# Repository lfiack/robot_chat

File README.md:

# robot_chat
My (as a prof) take at building a cat/mouse robot

## Make the project work
This project uses a submodule for the KiCAD library. To get it properly, use the `--recursive` option when cloning the repo :

```bash
git clone --recursive git@github.com:lfiack/robot_chat.git
```

If you forgot the `--recursive` option (as I do quite often), you can type the following command :

```bash
git submodule update --init --recursive
```

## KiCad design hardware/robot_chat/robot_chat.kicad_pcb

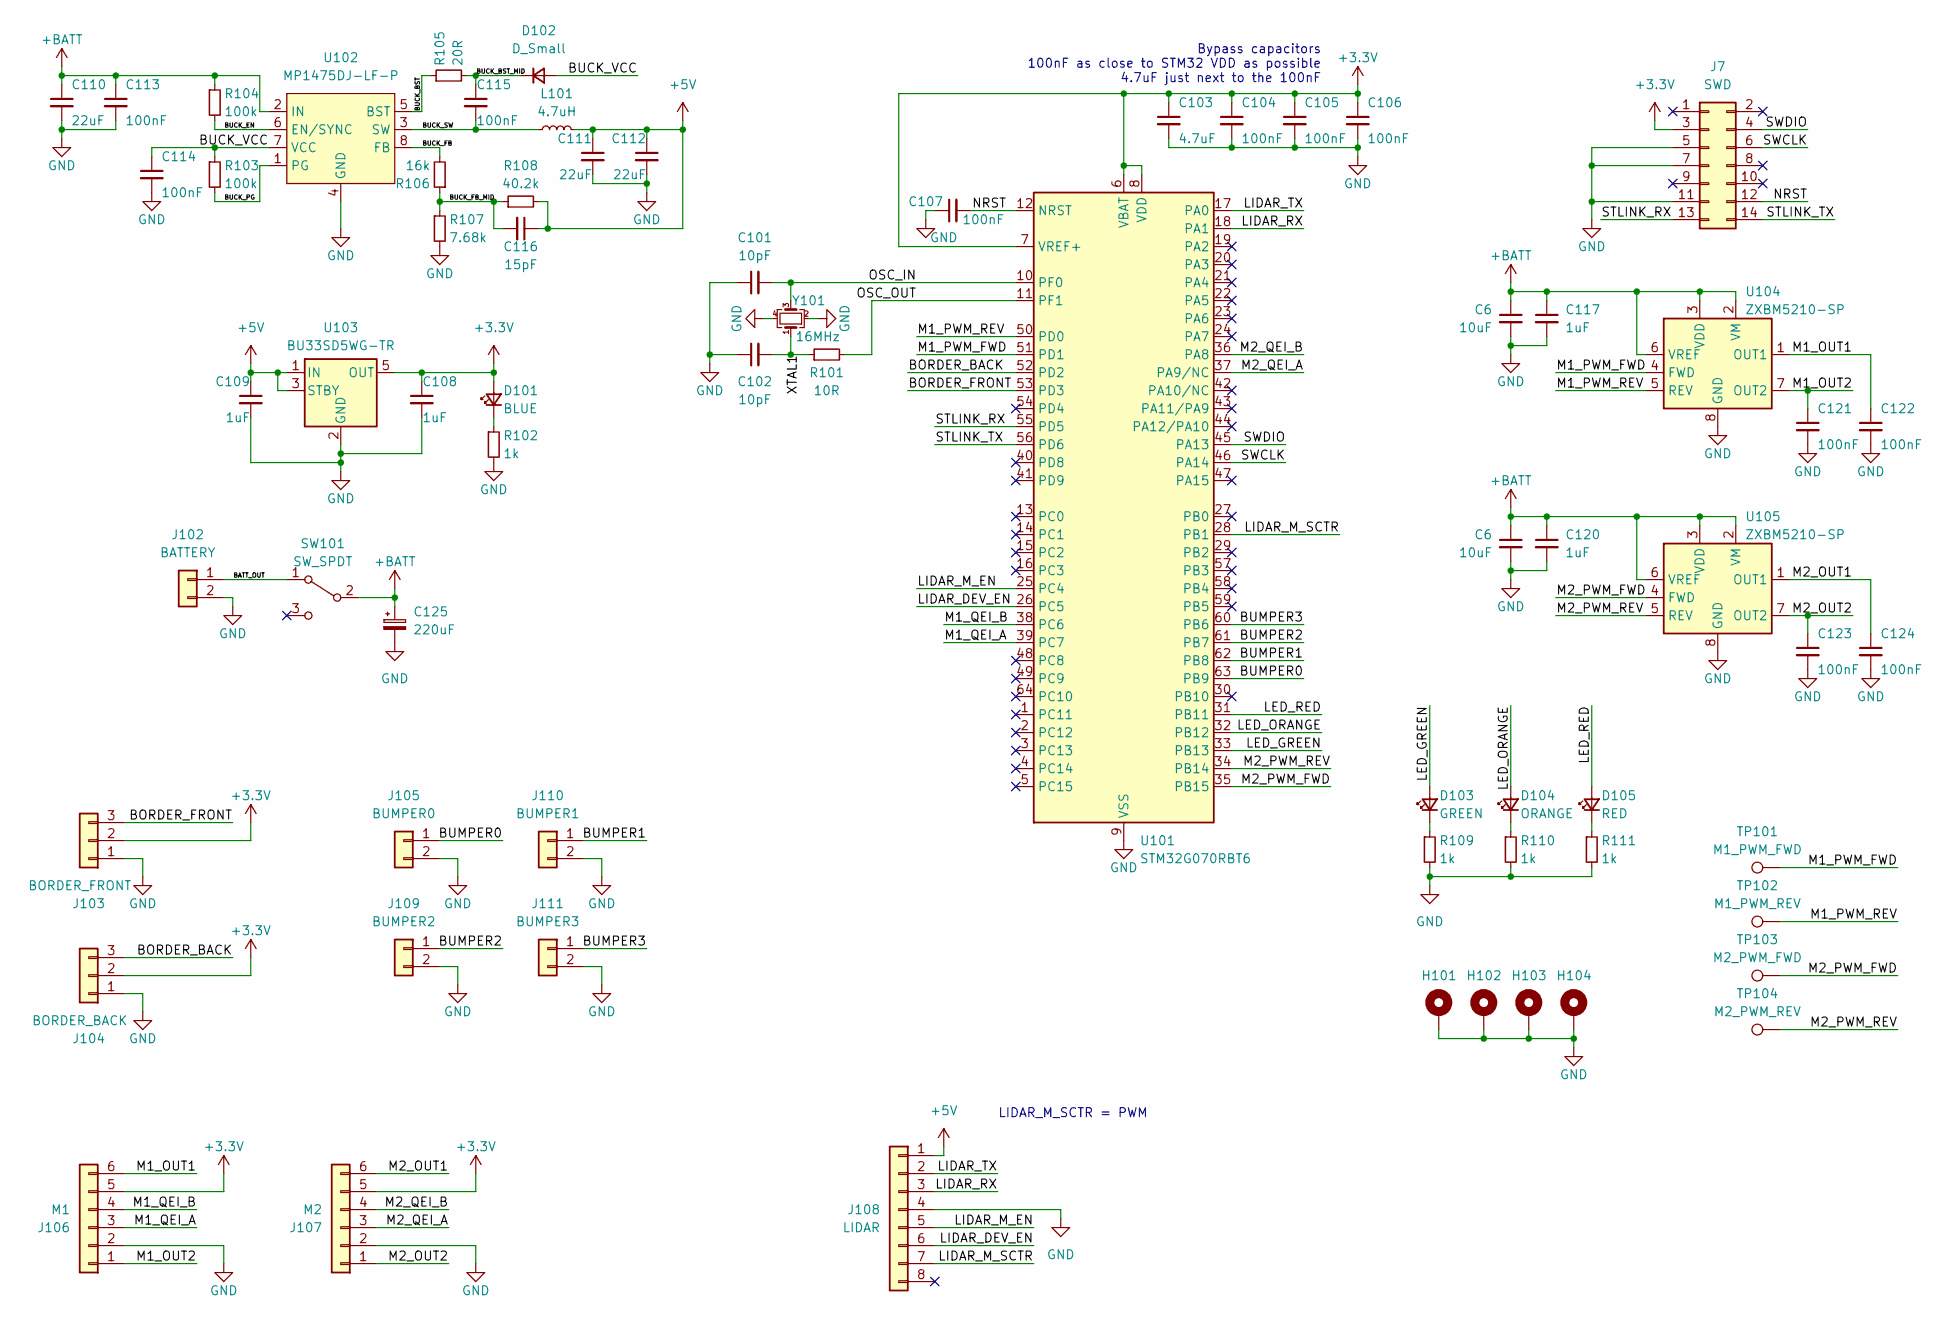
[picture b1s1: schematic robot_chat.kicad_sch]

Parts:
C6: 10uF; C_0603_1608Metric_Pad1.08x0.95mm_HandSolder; Farnell 2113070
C101, C102: 10pF; C_0603_1608Metric
C103: 4.7uF; C_0603_1608Metric
C104, C105, C106, C107, C113, C114, C115, C121, C122, C123, C124: 100nF; C_0603_1608Metric
C108, C109, C117, C120: 1uF; C_0603_1608Metric
C110, C111, C112: 22uF; C_0805_2012Metric
C116: 15pF; C_0603_1608Metric
C125: 220uF; CP_Elec_8x10.5
D101: BLUE; LED_0603_1608Metric
D102: D_Small; D_SOD-323
D103: GREEN; LED_0603_1608Metric
D104: ORANGE; LED_0603_1608Metric
D105: RED; LED_0603_1608Metric
H101, H102, H103, H104: MountingHole_Pad; MountingHole_3.2mm_M3_Pad_Via
J7: Conn_02x07_Odd_Even; PinHeader_2x07_P1.27mm_Vertical_SMD; Farnell 3226055
J102: BATTERY; JST_XH_S2B-XH-A_1x02_P2.50mm_Horizontal
J103: BORDER_FRONT; JST_XH_S3B-XH-A_1x03_P2.50mm_Horizontal
J104: BORDER_BACK; JST_XH_S3B-XH-A_1x03_P2.50mm_Horizontal
J105: BUMPER0; JST_XH_S2B-XH-A_1x02_P2.50mm_Horizontal
J106: M1; JST_XH_S6B-XH-A_1x06_P2.50mm_Horizontal
J107: M2; JST_XH_S6B-XH-A_1x06_P2.50mm_Horizontal
J108: LIDAR; JST_XH_S8B-XH-A_1x08_P2.50mm_Horizontal
J109: BUMPER2; JST_XH_S2B-XH-A_1x02_P2.50mm_Horizontal
J110: BUMPER1; JST_XH_S2B-XH-A_1x02_P2.50mm_Horizontal
J111: BUMPER3; JST_XH_S2B-XH-A_1x02_P2.50mm_Horizontal
L101: 4.7uH; L_1008_2520Metric; Farnell 2530076
R101: 10R; R_0603_1608Metric
R102, R109, R110, R111: 1k; R_0603_1608Metric
R103, R104: 100k; R_0603_1608Metric
R105: 20R; R_0603_1608Metric
R106: 16k; R_0603_1608Metric
R107: 7.68k; R_0603_1608Metric
R108: 40.2k; R_0603_1608Metric
SW101: SW_SPDT; Toggle_Switch
TP101: M1_PWM_FWD; TestPoint_Pad_D1.5mm
TP102: M1_PWM_REV; TestPoint_Pad_D1.5mm
TP103: M2_PWM_FWD; TestPoint_Pad_D1.5mm
TP104: M2_PWM_REV; TestPoint_Pad_D1.5mm
U101: STM32G070RBT6; LQFP-64_10x10mm_P0.5mm
U102: MP1475DJ-LF-P; TSOT-23-8
U103: BU33SD5WG-TR; SOT-23-5
U104, U105: ZXBM5210-SP; Diodes_SO-8EP
Y101: 16MHz; Crystal_SMD_EuroQuartz_MT-4Pin_3.2x2.5mm; Farnell 2853935

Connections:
+3.3V: C103.1, C104.1, C105.1, C106.1, C108.1, D101.2 (A), J7.3, J103.2, J104.2, J106.5, J107.5, U101.6 (VBAT), U101.7 (VREF+), U101.8 (VDD), U103.5 (OUT)
+5V: C109.1, C111.1, C112.1, C116.1, J108.1, L101.2, R108.2, U103.1 (IN), U103.3 (STBY)
+BATT: C6.1, C110.1, C113.1, C117.1, C120.1, C125.1, R104.1, SW101.2 (B), U102.2 (IN), U104.2 (VM), U104.3 (VDD), U104.6 (VREF), U105.2 (VM), U105.3 (VDD), U105.6 (VREF); also elsewhere on the board
/BATT_OUT: J102.1, SW101.1 (A)
/BORDER_BACK: J104.3, U101.52 (PD2)
/BORDER_FRONT: J103.3, U101.53 (PD3)
/BUCK_BST: R105.1, U102.5 (BST)
/BUCK_BST_MID: C115.1, D102.1 (K), R105.2
/BUCK_EN: R104.2, U102.6 (EN/SYNC)
/BUCK_FB: R106.2, U102.8 (FB)
/BUCK_FB_MID: C116.2, R106.1, R107.1, R108.1
/BUCK_PG: R103.2, U102.1 (PG)
/BUCK_SW: C115.2, L101.1, U102.3 (SW)
/BUCK_VCC: C114.1, D102.2 (A), R103.1, U102.7 (VCC)
/BUMPER0: J105.1, U101.63 (PB9)
/BUMPER1: J110.1, U101.62 (PB8)
/BUMPER2: J109.1, U101.61 (PB7)
/BUMPER3: J111.1, U101.60 (PB6)
/LED_GREEN: D103.2 (A), U101.33 (PB13)
/LED_ORANGE: D104.2 (A), U101.32 (PB12)
/LED_RED: D105.2 (A), U101.31 (PB11)
/LIDAR_DEV_EN: J108.6, U101.26 (PC5)
/LIDAR_M_EN: J108.5, U101.25 (PC4)
/LIDAR_M_SCTR: J108.7, U101.28 (PB1)
/LIDAR_RX: J108.3, U101.18 (PA1)
/LIDAR_TX: J108.2, U101.17 (PA0)
/M1_OUT1: C122.1, J106.6, U104.1 (OUT1)
/M1_OUT2: C121.1, J106.1, U104.7 (OUT2)
/M1_PWM_FWD: TP101.1, U101.51 (PD1), U104.4 (FWD)
/M1_PWM_REV: TP102.1, U101.50 (PD0), U104.5 (REV)
/M1_QEI_A: J106.3, U101.39 (PC7)
/M1_QEI_B: J106.4, U101.38 (PC6)
/M2_OUT1: C124.1, J107.6, U105.1 (OUT1)
/M2_OUT2: C123.1, J107.1, U105.7 (OUT2)
/M2_PWM_FWD: TP103.1, U101.35 (PB15), U105.4 (FWD)
/M2_PWM_REV: TP104.1, U101.34 (PB14), U105.5 (REV)
/M2_QEI_A: J107.3, U101.37 (PA9/NC)
/M2_QEI_B: J107.4, U101.36 (PA8)
/NRST: C107.2, J7.12, U101.12 (NRST)
/OSC_IN: C101.2, U101.10 (PF0), Y101.3
/OSC_OUT: R101.2, U101.11 (PF1)
/STLINK_RX: J7.13, U101.55 (PD5)
/STLINK_TX: J7.14, U101.56 (PD6)
/SWCLK: J7.6, U101.46 (PA14)
/SWDIO: J7.4, U101.45 (PA13)
/XTAL1: C102.2, R101.1, Y101.1
GND: C6.2, C101.1, C102.1, C103.2, C104.2, C105.2, C106.2, C107.1, C108.2, C109.2, C110.2, C111.2, C112.2, C113.2, C114.2, C117.2, C120.2, C121.2, C122.2, C123.2, C124.2, C125.2, H101.1, H102.1, H103.1, H104.1, J7.5, J7.7, J7.11, J102.2, J103.1, J104.1, J105.2, J106.2, J107.2, J108.4, J109.2, J110.2, J111.2, R102.2, R107.2, R109.2, R110.2, R111.2, U101.9 (VSS), U102.4 (GND), U103.2 (GND), U104.8 (GND), U104.9 (GND), U105.8 (GND), U105.9 (GND), Y101.2, Y101.4; also elsewhere on the board
unnamed: D101.1 (K), R102.1
unnamed: D103.1 (K), R109.1
unnamed: D104.1 (K), R110.1
unnamed: D105.1 (K), R111.1

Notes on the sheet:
Bypass capacitors 100nF as close to STM32 VDD as possible 4.7uF just next to the 100nF
LIDAR_M_SCTR = PWM

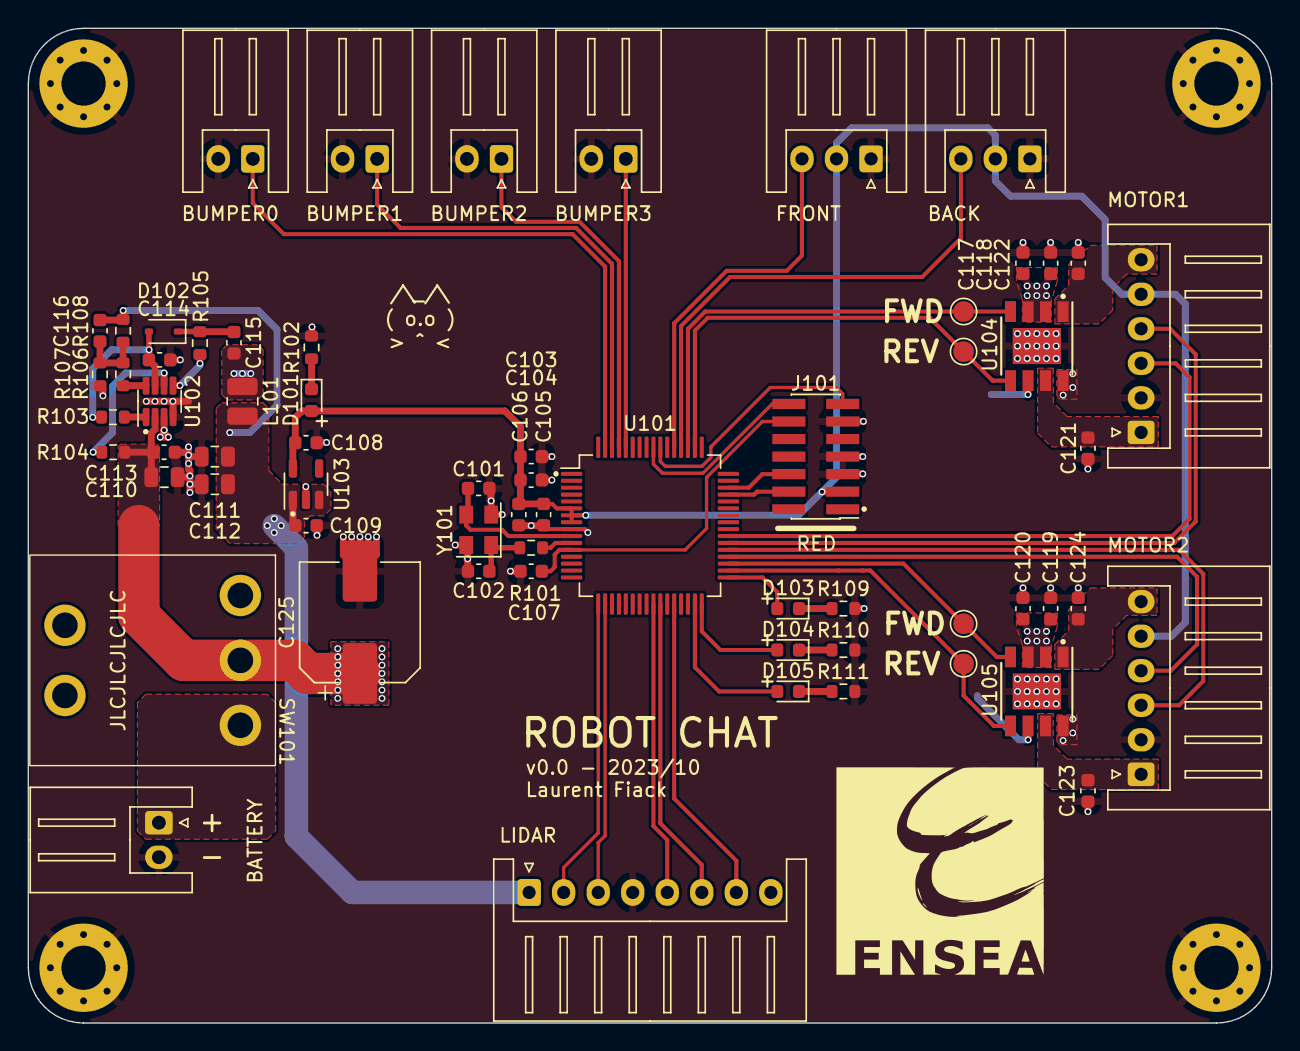
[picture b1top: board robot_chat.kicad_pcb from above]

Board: 2 copper layers, 90.0 x 72.0 mm, 68 parts (0 on the bottom side), 51 nets.

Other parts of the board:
C6#2: 10uF; C_0603_1608Metric

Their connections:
+BATT: C6#2.1; also elsewhere on the board
GND: C6#2.2; also elsewhere on the board

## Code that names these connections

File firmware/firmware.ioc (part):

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Mcu.Name=STM32G070RBTx
Mcu.Package=LQFP64
Mcu.UserName=STM32G070RBTx
PA0.Mode=Asynchronous
PA0.Signal=USART4_TX
PA1.Mode=Asynchronous
PA1.Signal=USART4_RX
PA13.Mode=Serial_Wire
PA13.Signal=SYS_SWDIO
PA14-BOOT0.Mode=Serial_Wire
PA14-BOOT0.Signal=SYS_SWCLK
PA8.GPIOParameters=GPIO_Label
PA8.GPIO_Label=M1_QEI_B
PA8.Signal=S_TIM1_CH1
PA9.GPIOParameters=GPIO_Label
PA9.GPIO_Label=M1_QEI_A
PA9.Signal=S_TIM1_CH2
PB1.GPIOParameters=GPIO_Label
PB1.GPIO_Label=LIDAR_PWM
PB1.Signal=S_TIM14_CH1
PB11.Signal=GPIO_Output
PB12.Signal=GPIO_Output
PB13.Signal=GPIO_Output
PB14.GPIOParameters=GPIO_Label
PB14.GPIO_Label=M1_PWM_FWD
PB14.Signal=S_TIM15_CH1
PB15.GPIOParameters=GPIO_Label
PB15.GPIO_Label=M1_PWM_REV
PB15.Signal=S_TIM15_CH2
PB6.Signal=GPXTI6
PB7.Signal=GPXTI7
PB8.Signal=GPXTI8
PB9.Signal=GPXTI9
PC4.Signal=GPIO_Output
PC5.Signal=GPIO_Output
PC6.GPIOParameters=GPIO_Label
PC6.GPIO_Label=M2_QEI_B
PC6.Signal=S_TIM3_CH1
PC7.GPIOParameters=GPIO_Label
PC7.GPIO_Label=M2_QEI_A
PC7.Signal=S_TIM3_CH2
PD0.GPIOParameters=GPIO_Label
PD0.GPIO_Label=M2_PWM_FWD
PD0.Signal=S_TIM16_CH1
PD1.GPIOParameters=GPIO_Label
PD1.GPIO_Label=M2_PWM_REV
PD1.Signal=S_TIM17_CH1
PD2.Signal=GPXTI2
PD3.Signal=GPXTI3
PD5.Mode=Asynchronous
PD5.Signal=USART2_TX
PD6.Mode=Asynchronous
PD6.Signal=USART2_RX
PF0-OSC_IN\ (PF0).Mode=HSE-External-Oscillator
PF0-OSC_IN\ (PF0).Signal=RCC_OSC_IN
PF1-OSC_OUT\ (PF1).Mode=HSE-External-Oscillator
PF1-OSC_OUT\ (PF1).Signal=RCC_OSC_OUT
RCC.HSE_VALUE=16000000
RCC.SYSCLKFreq_VALUE=64000000
RCC.SYSCLKSource=RCC_SYSCLKSOURCE_PLLCLK
board=custom

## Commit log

2023-10-16 kicad lib + README
2023-10-16 started schematic
2023-10-16 schematic
2023-10-19 place + started routing
2023-10-19 routage
2023-10-20 routing
